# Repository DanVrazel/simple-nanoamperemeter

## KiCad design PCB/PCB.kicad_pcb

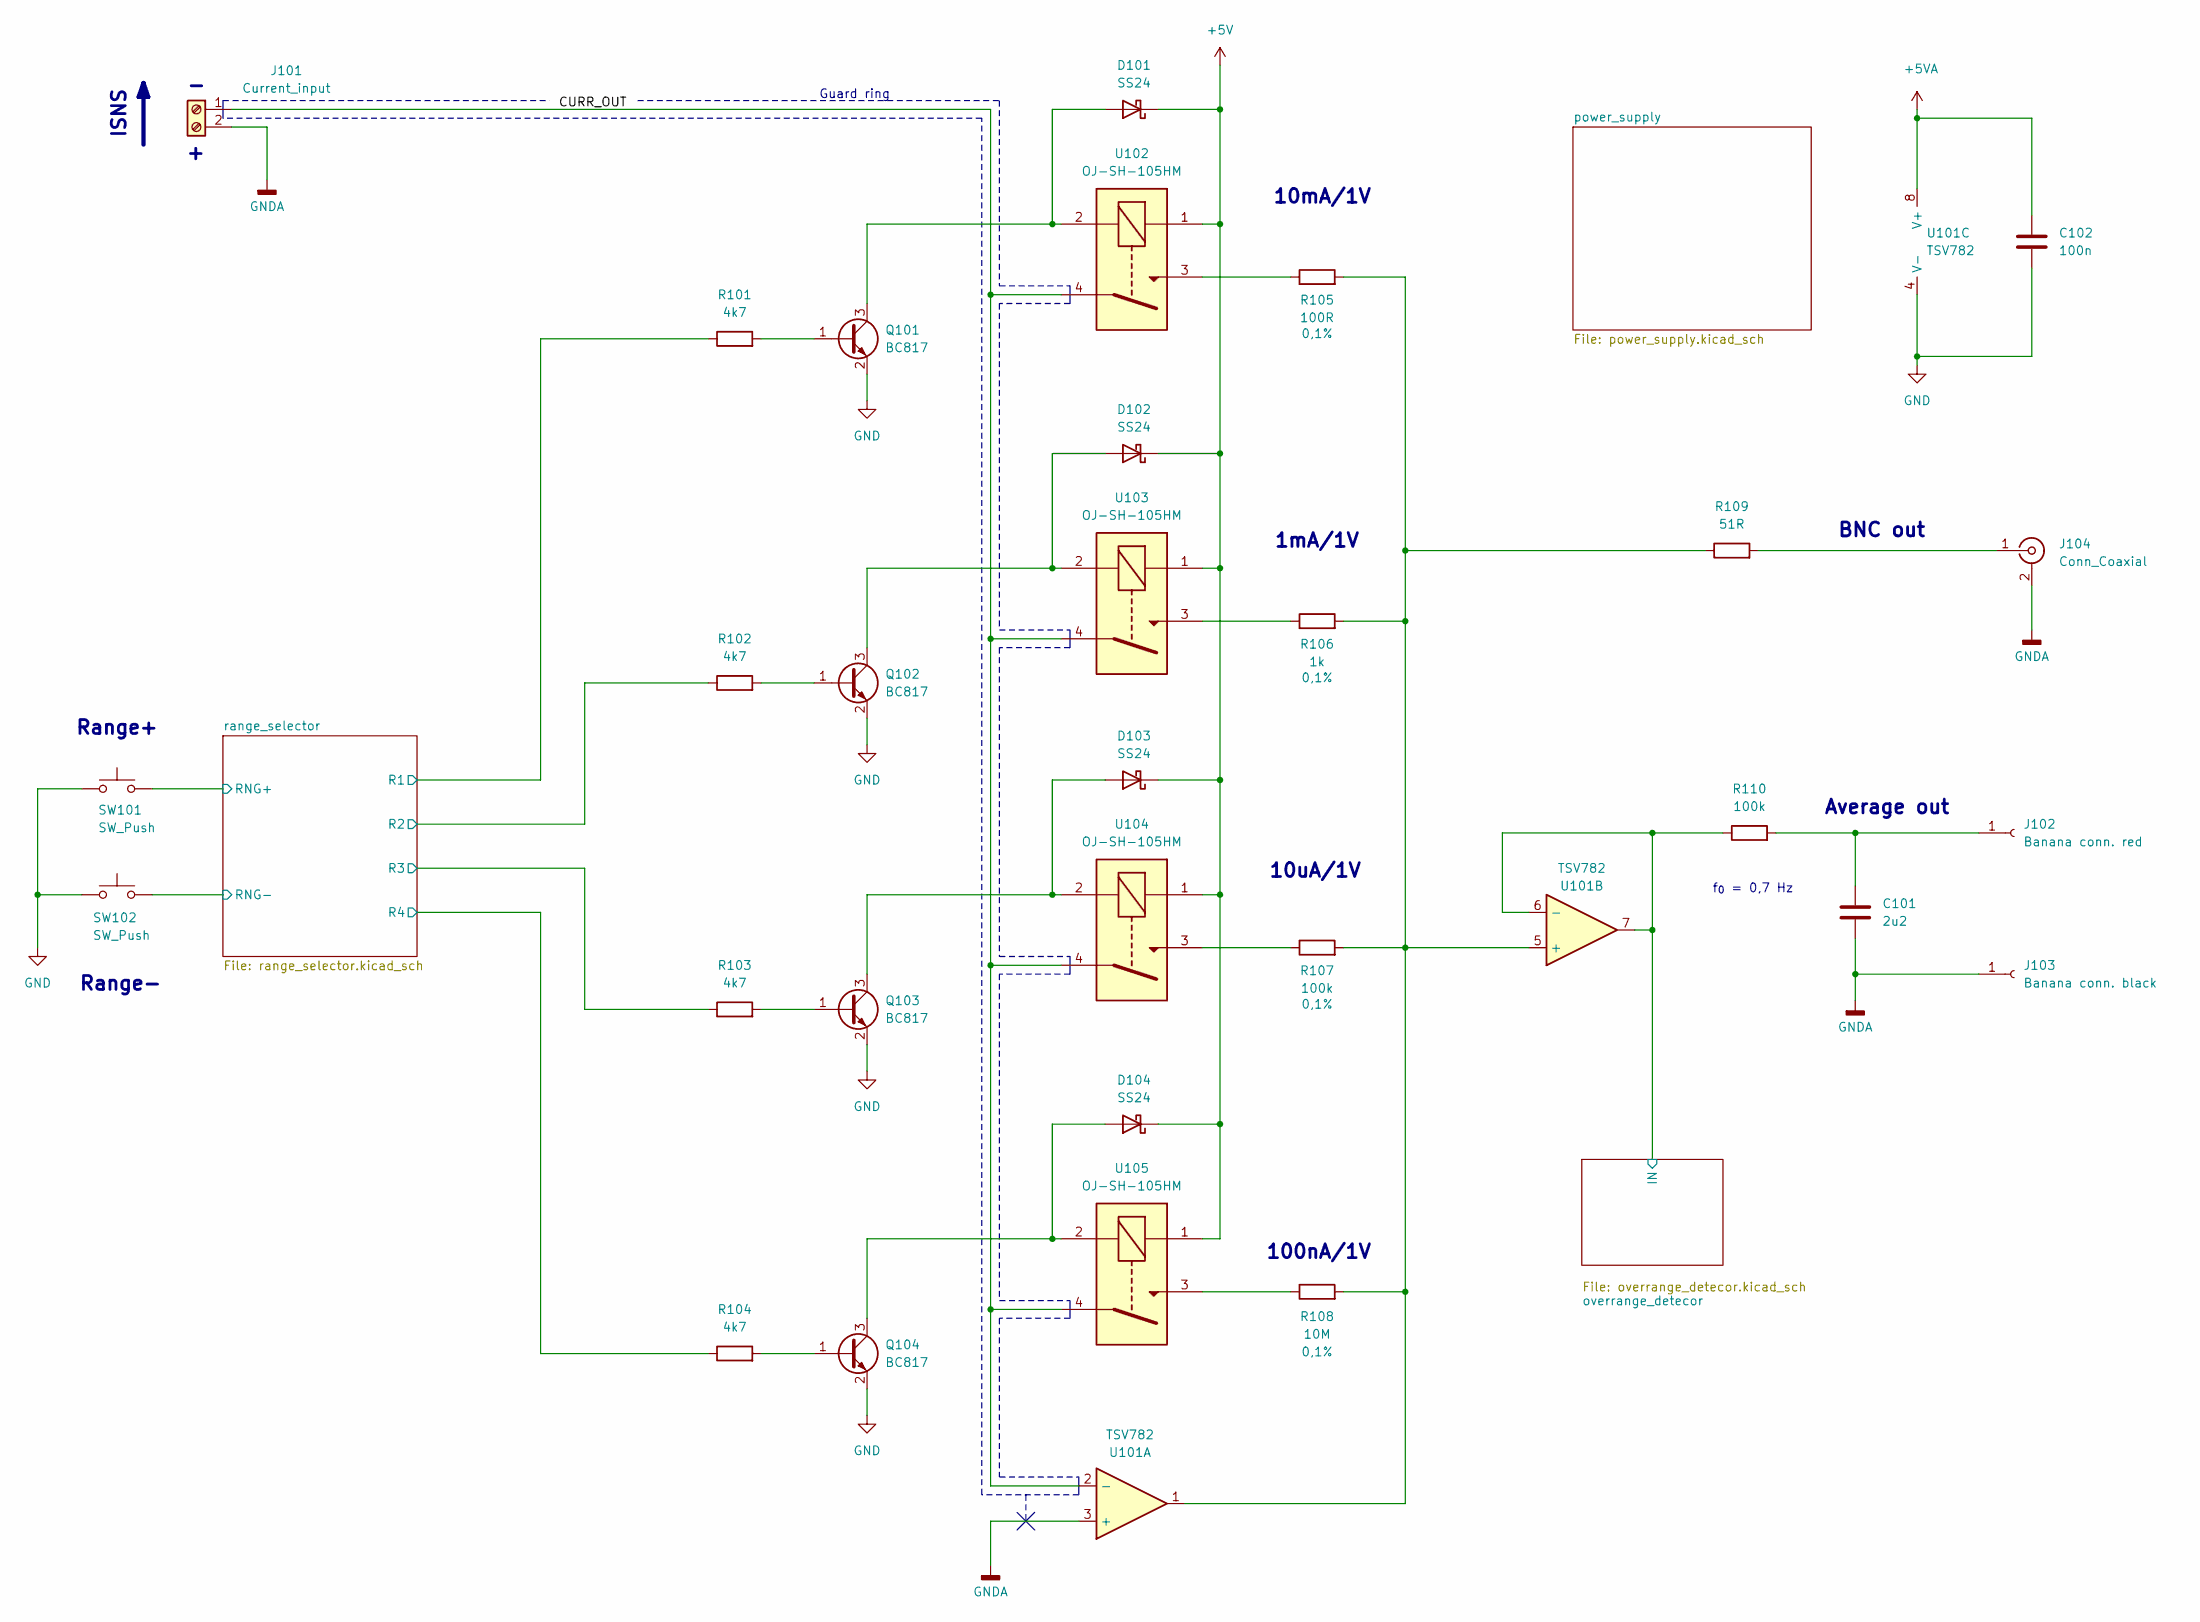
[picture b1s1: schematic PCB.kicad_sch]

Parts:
C101: 2u2; C_0603_1608Metric
C102: 100n; C_0603_1608Metric
D101, D102, D103, D104: SS24; SOD-123LF
J101: Current_input; Terminal Block 2x3,5mm
J102: Banana conn. red; J.40024.2
J103: Banana conn. black; J.40024.2
J104: Conn_Coaxial; BNC_Amphenol_B6252HB-NPP3G-50_Horizontal
Q101, Q102, Q103, Q104: BC817; SOT-23
R101, R102, R103, R104: 4k7; R_0603_1608Metric
R105: 100R; R_0603_1608Metric
R106: 1k; R_0603_1608Metric
R107, R110: 100k; R_0603_1608Metric
R108: 10M; R_1206_3216Metric; Mouser MCA1206MD1005BP500
R109: 51R; R_0603_1608Metric
SW101, SW102: SW_Push; SW_Tactile_SPST_Angled_PTS645Vx83-2LFS
U101: TSV782; SOIC-8
U102, U103, U104, U105: OJ-SH-105HM; TE Connectivity Relay

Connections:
+5V: D101.1 (K), D102.1 (K), D103.1 (K), D104.1 (K), U102.1, U103.1, U104.1, U105.1; also elsewhere on the board
/CURR_OUT: J101.1, U101.2 (-), U102.4, U103.4, U104.4, U105.4
/overrange_detecor/IN: R110.1, U101.6 (-), U101.7; also elsewhere on the board
/range_selector/R1: R101.1; also elsewhere on the board
/range_selector/R2: R102.1; also elsewhere on the board
/range_selector/R3: R103.1; also elsewhere on the board
/range_selector/R4: R104.1; also elsewhere on the board
/range_selector/RNG+: SW101.2; also elsewhere on the board
/range_selector/RNG-: SW102.2; also elsewhere on the board
GNDA: C101.2, J101.2, J103.1, J104.2 (Ext), U101.3 (+); also elsewhere on the board
unnamed: D101.2 (A), Q101.3 (C), U102.2
unnamed: D102.2 (A), Q102.3 (C), U103.2
unnamed: D103.2 (A), Q103.3 (C), U104.2
unnamed: D104.2 (A), Q104.3 (C), U105.2
unnamed: C101.1, J102.1, R110.2
unnamed: J104.1 (In), R109.2
unnamed: Q101.1 (B), R101.2
unnamed: Q102.1 (B), R102.2
unnamed: Q103.1 (B), R103.2
unnamed: Q104.1 (B), R104.2
unnamed: R105.1, U102.3
unnamed: R106.1, U103.3
unnamed: R107.1, U104.3
unnamed: R108.1, U105.3
unnamed: R105.2, R106.2, R107.2, R108.2, R109.1, U101.1, U101.5 (+)

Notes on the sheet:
10mA/1V
ISNS
Range+
Guard ring
10uA/1V
Average out
100nA/1V
1mA/1V
f_{0} = 0,7 Hz
Range-
BNC out

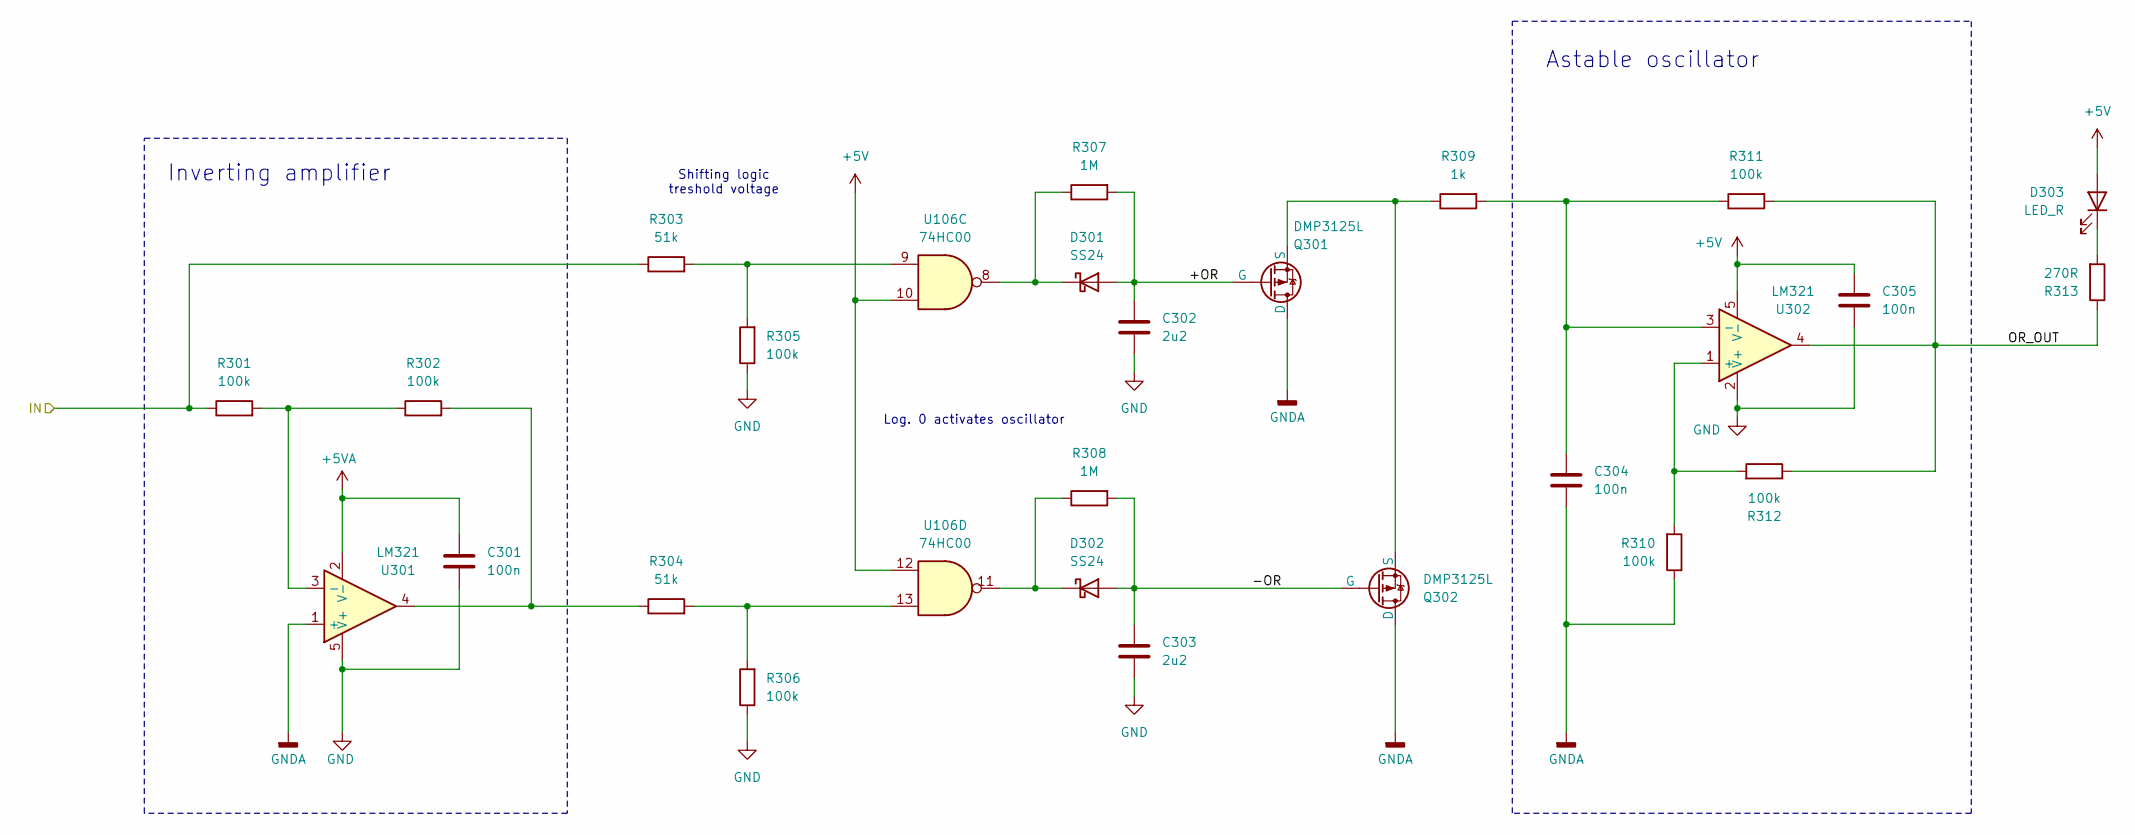
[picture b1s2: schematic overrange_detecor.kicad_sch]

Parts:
C301, C304, C305: 100n; C_0603_1608Metric
C302, C303: 2u2; C_0603_1608Metric
D301, D302: SS24; SOD-123LF
D303: LED_R; LED_D3.0mm
Q301, Q302: DMP3125L; SOT23-3
R301, R302, R305, R306, R310, R311, R312: 100k; R_0603_1608Metric
R303, R304: 51k; R_0603_1608Metric
R307, R308: 1M; R_0603_1608Metric
R309: 1k; R_0603_1608Metric
R313: 270R; R_0603_1608Metric
U106: 74HC00; SOIC-14 3.9x8.6mm P1.27mm
U301, U302: LM321; SOT-23-5L

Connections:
+5V: C305.1, D303.2 (A), U106.10, U106.12, U302.5 (V-); also elsewhere on the board
/overrange_detecor/+OR: C302.1, D301.2 (A), Q301.1 (G), R307.2
/overrange_detecor/-OR: C303.1, D302.2 (A), Q302.1 (G), R308.2
/overrange_detecor/IN: R301.1, R303.1; also elsewhere on the board
/overrange_detecor/OR_OUT: R311.2, R312.1, R313.1, U302.4
GNDA: C304.2, Q301.2 (D), Q302.2 (D), R310.1, U301.1 (+); also elsewhere on the board
unnamed: D301.1 (K), R307.1, U106.8
unnamed: D302.1 (K), R308.1, U106.11
unnamed: D303.1 (K), R313.2
unnamed: Q301.3 (S), Q302.3 (S), R309.1
unnamed: R302.2, R304.1, U301.4
unnamed: R303.2, R305.2, U106.9
unnamed: R304.2, R306.2, U106.13
unnamed: R301.2, R302.1, U301.3 (-)
unnamed: R310.2, R312.2, U302.1 (+)
unnamed: C304.1, R309.2, R311.1, U302.3 (-)

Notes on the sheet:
Astable oscillator
Log. 0 activates oscillator
Inverting amplifier
Shifting logic treshold voltage

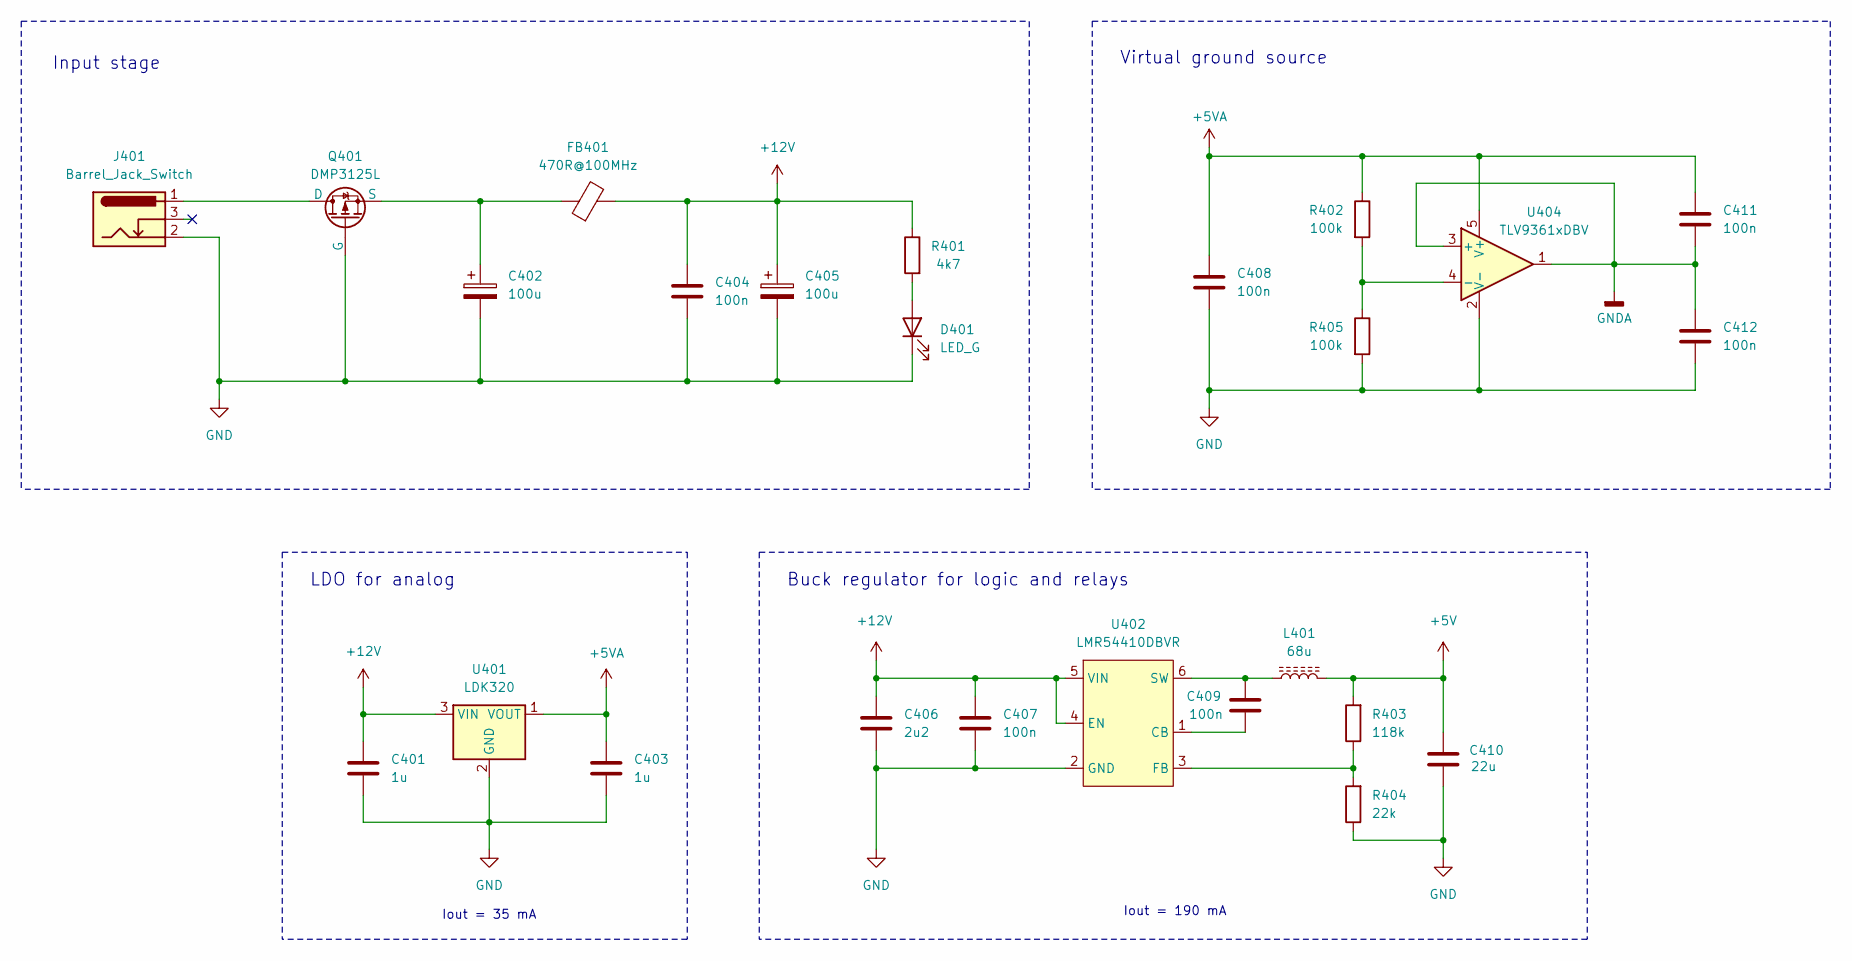
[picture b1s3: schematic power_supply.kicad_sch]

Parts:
C401, C403: 1u; C_0603_1608Metric
C402, C405: 100u; C_Radial_D6.3mm_H11.0mm_P2.50mm
C404, C407, C408, C409, C411, C412: 100n; C_0603_1608Metric
C406: 2u2; C_0603_1608Metric
C410: 22u; C_0805_2012Metric
D401: LED_G; LED_D3.0mm_Clear
FB401: 470R@100MHz; L_0603_1608Metric
J401: Barrel_Jack_Switch; Barrel jack 6,4mm
L401: 68u; Shielded L 6x6x4.2mm
Q401: DMP3125L; SOT23-3
R401: 4k7; R_0603_1608Metric
R402, R405: 100k; R_0603_1608Metric
R403: 118k; R_0603_1608Metric
R404: 22k; R_0603_1608Metric
U401: LDK320; SOT-89-3
U402: LMR54410DBVR; SOP-6
U404: TLV9361xDBV; SOT-23-5L

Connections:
+5V: C410.2, L401.2, R403.2; also elsewhere on the board
+12V: C401.1, C404.1, C405.1, C406.1, C407.1, FB401.2, R401.1, U401.3 (VIN), U402.4 (EN), U402.5 (VIN)
GNDA: C411.2, C412.1, U404.1, U404.3 (+); also elsewhere on the board
unnamed: D401.2 (A), R401.2
unnamed: J401.1, Q401.2 (D)
unnamed: C402.1, FB401.1, Q401.3 (S)
unnamed: C409.1, U402.1 (CB)
unnamed: R403.1, R404.2, U402.3 (FB)
unnamed: C409.2, L401.1, U402.6 (SW)
unnamed: R402.2, R405.1, U404.4 (-)

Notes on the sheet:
Iout = 190 mA
Buck regulator for logic and relays
LDO for analog
Iout = 35 mA
Virtual ground source
Input stage

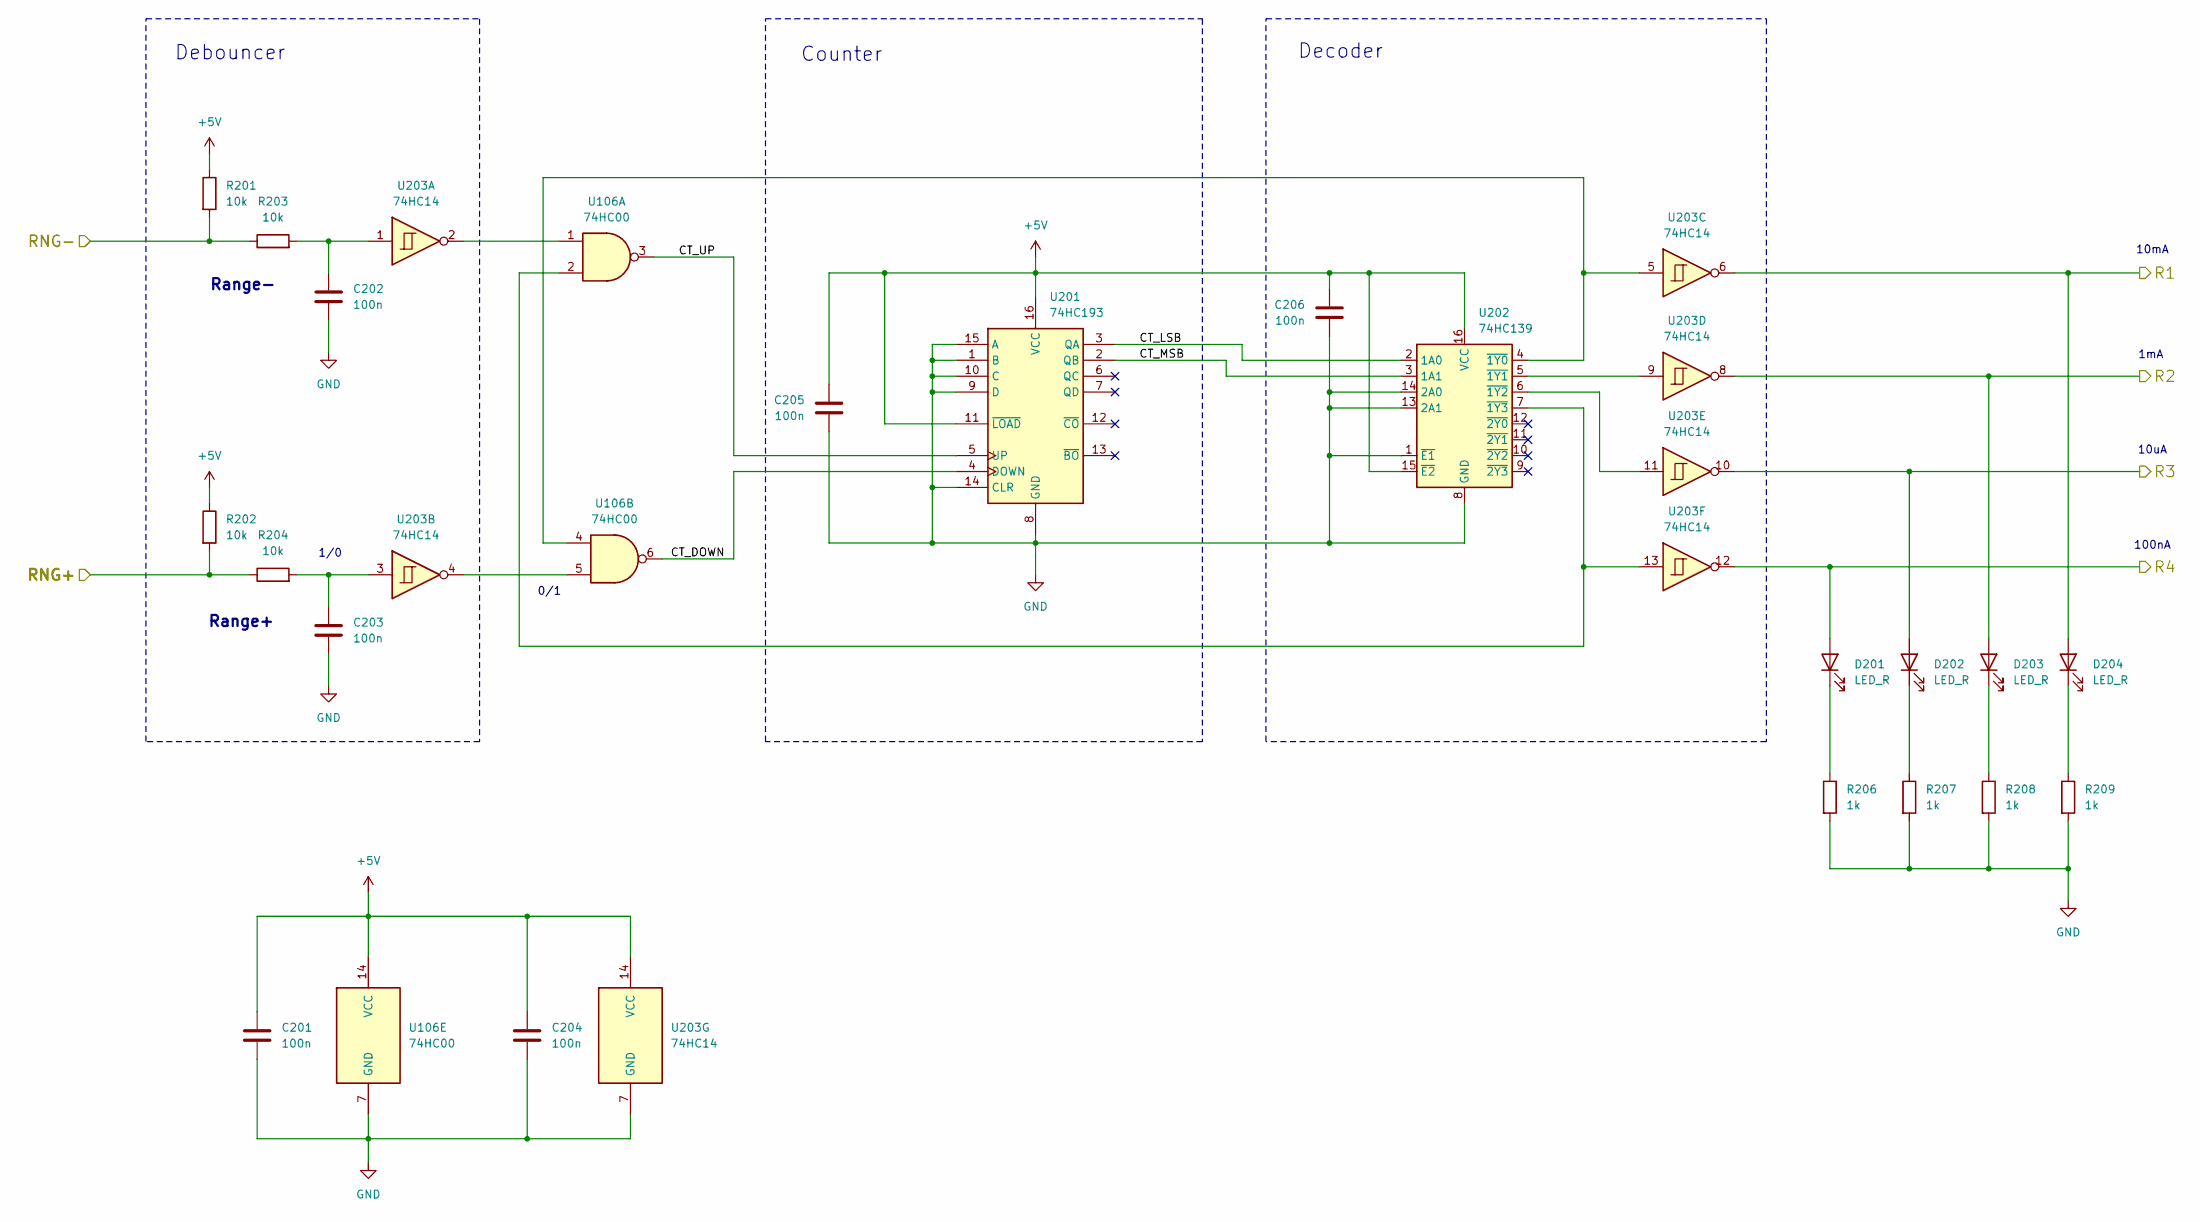
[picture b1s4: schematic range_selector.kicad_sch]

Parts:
C201, C202, C203, C204, C205, C206: 100n; C_0603_1608Metric
D201, D202, D203, D204: LED_R; LED_D3.0mm
R201, R202, R203, R204: 10k; R_0603_1608Metric
R206, R207, R208, R209: 1k; R_0603_1608Metric
U106: 74HC00; SOIC-14 3.9x8.6mm P1.27mm
U201: 74HC193; SOIC-16 3.9x9.9mm P1.27mm
U202: 74HC139; SOIC-16 3.9x9.9mm P1.27mm
U203: 74HC14; SOIC-14 3.9x8.6mm P1.27mm

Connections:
+5V: C201.1, C204.1, C205.1, C206.1, R201.1, R202.1, U106.14 (VCC), U201.11 (~LOAD), U201.16 (VCC), U202.15 (~E2), U202.16 (VCC), U203.14 (VCC); also elsewhere on the board
/range_selector/CT_DOWN: U106.6, U201.4 (DOWN)
/range_selector/CT_LSB: U201.3 (QA), U202.2 (1A0)
/range_selector/CT_MSB: U201.2 (QB), U202.3 (1A1)
/range_selector/CT_UP: U106.3, U201.5 (UP)
/range_selector/R1: D204.2 (A), U203.6; also elsewhere on the board
/range_selector/R2: D203.2 (A), U203.8; also elsewhere on the board
/range_selector/R3: D202.2 (A), U203.10; also elsewhere on the board
/range_selector/R4: D201.2 (A), U203.12; also elsewhere on the board
/range_selector/RNG+: R202.2, R204.1; also elsewhere on the board
/range_selector/RNG-: R201.2, R203.1; also elsewhere on the board
unnamed: C202.1, R203.2, U203.1
unnamed: C203.1, R204.2, U203.3
unnamed: D201.1 (K), R206.1
unnamed: D202.1 (K), R207.1
unnamed: D203.1 (K), R208.1
unnamed: D204.1 (K), R209.1
unnamed: U106.1, U203.2
unnamed: U106.5, U203.4
unnamed: U106.4, U202.4 (~1Y0), U203.5
unnamed: U202.5 (~1Y1), U203.9
unnamed: U202.6 (~1Y2), U203.11
unnamed: U106.2, U202.7 (~1Y3), U203.13

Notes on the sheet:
Decoder
Counter
1/0
Range-
10mA
Range+
0/1
1mA
10uA
Debouncer
100nA

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
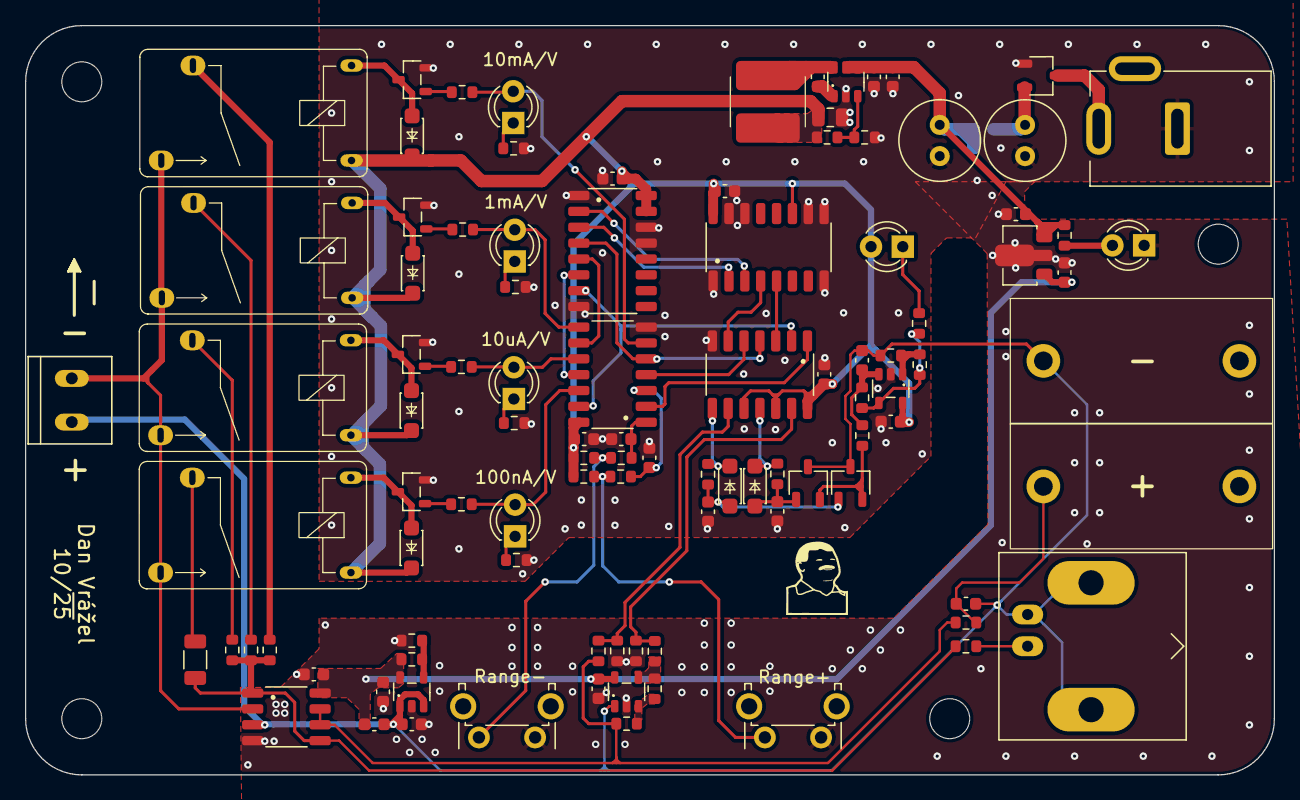
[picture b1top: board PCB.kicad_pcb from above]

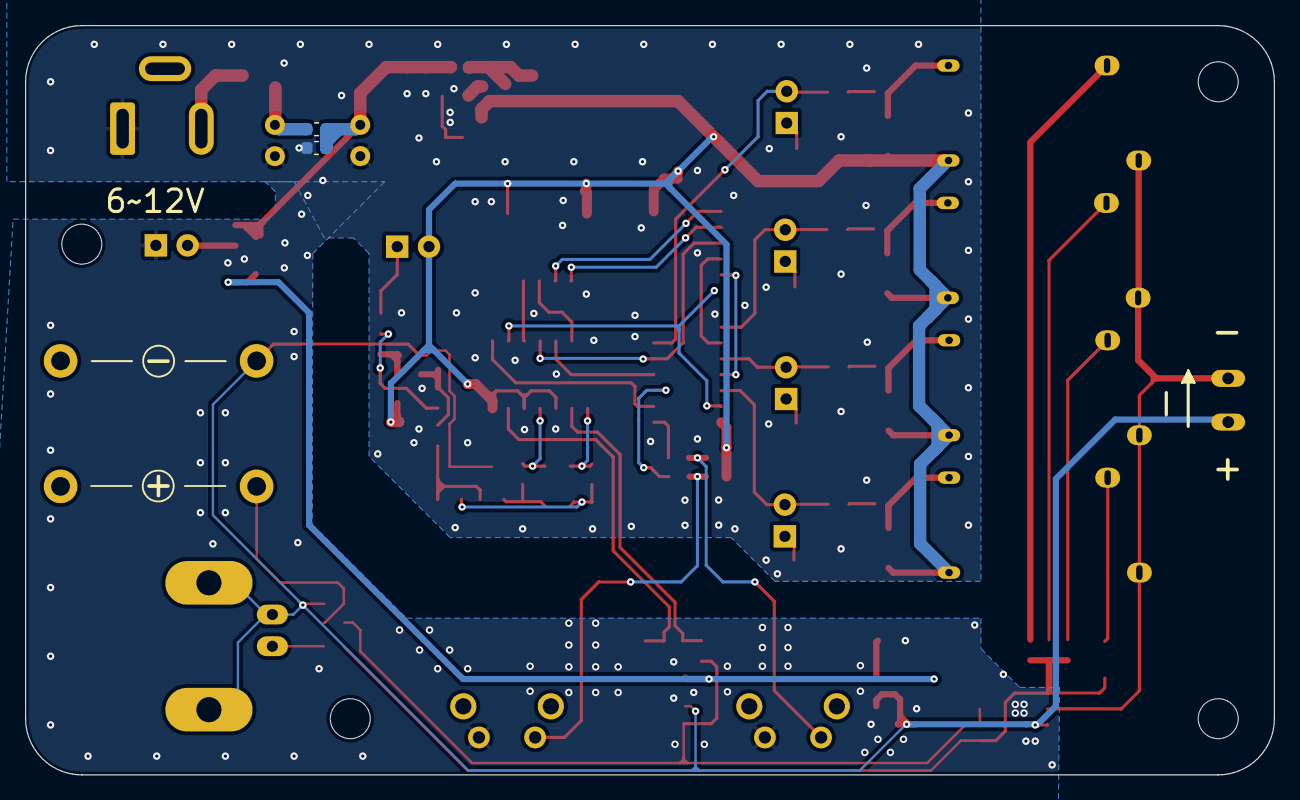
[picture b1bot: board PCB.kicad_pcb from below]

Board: 2 copper layers, 100.0 x 60.0 mm, 103 parts (2 on the bottom side), 64 nets.

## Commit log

2025-09-02 power supply
2025-09-03 schematic progress
2025-09-04 range switching
2025-09-04 astable op amp
2025-09-07 schematic roughly done
2025-09-08 footprints
2025-09-09 footprints and overrange detector timing
2025-09-12 start of layout
2025-09-14 rough layout done
2025-09-15 almost done
2025-09-16 rev 1 done
2025-10-04 changed BNC footprint
